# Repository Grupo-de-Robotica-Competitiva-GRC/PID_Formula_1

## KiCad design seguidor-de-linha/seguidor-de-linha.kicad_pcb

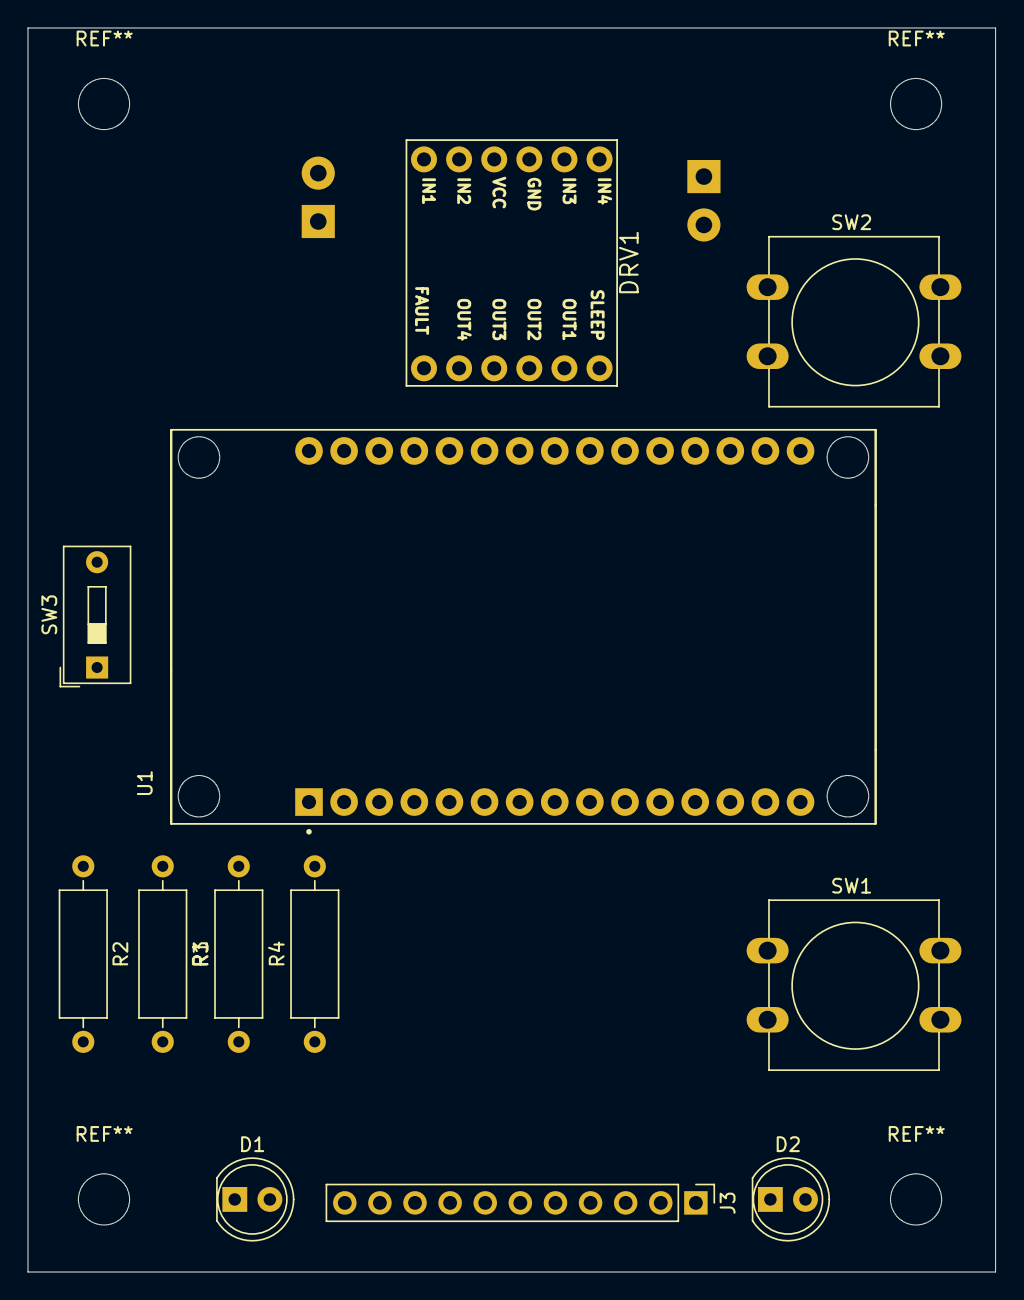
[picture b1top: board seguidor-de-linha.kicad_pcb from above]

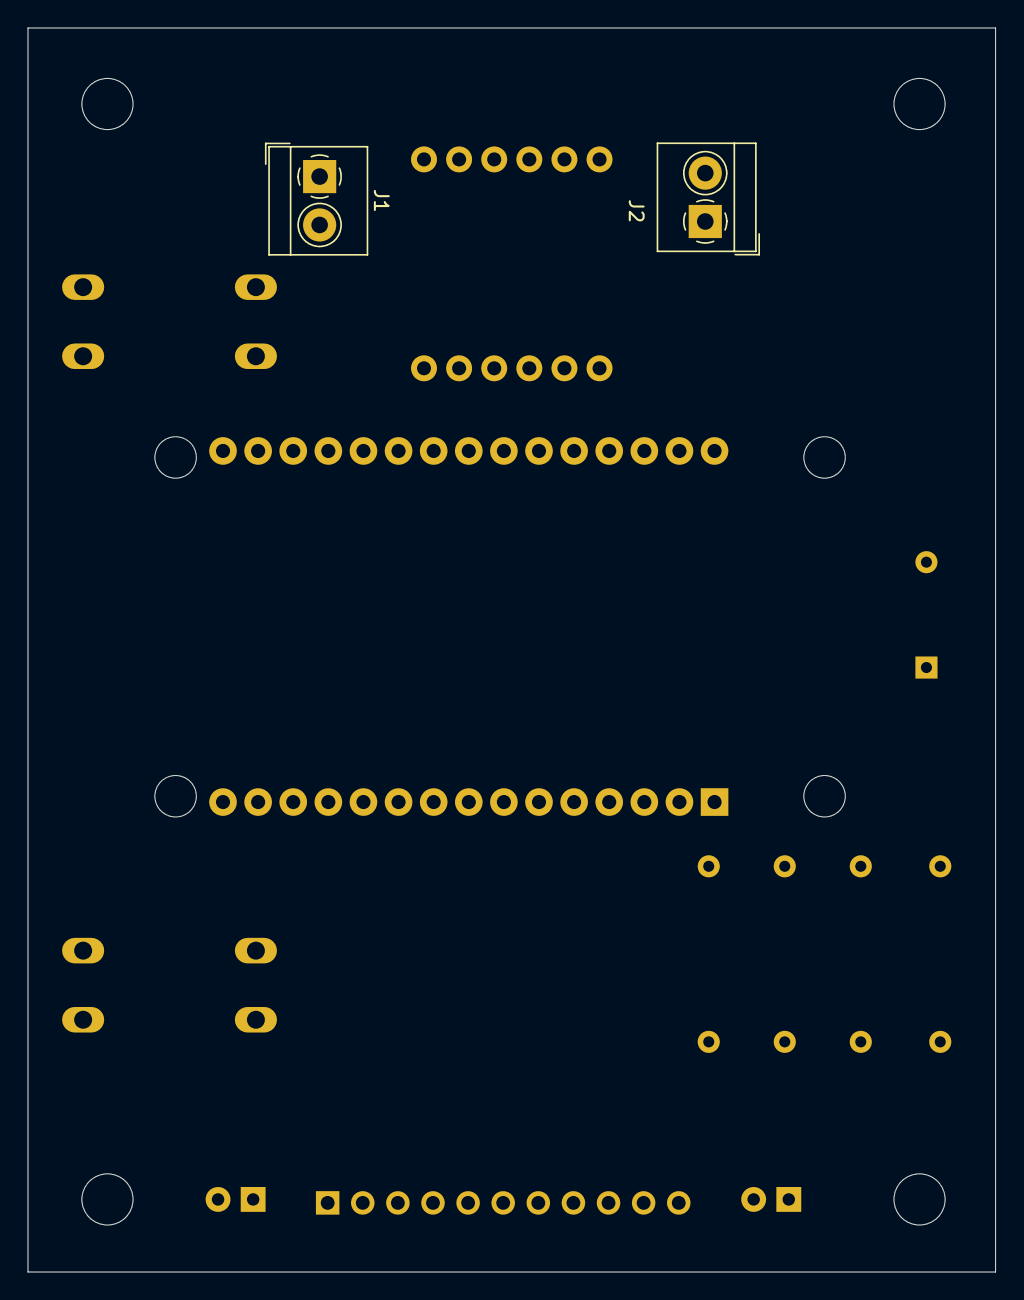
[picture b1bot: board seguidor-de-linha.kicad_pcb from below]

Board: 2 copper layers, 70.0 x 90.0 mm, 14 parts (2 on the bottom side), 26 nets, no tracks yet.

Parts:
D1, D2: LED; LED_D5.0mm
DRV1: drv8833; DRV8833 MOTOR DRIVER
J1, J2: Screw_Terminal_01x02; TerminalBlock_4Ucon_1x02_P3.50mm_Horizontal
J3: Conn_01x11_Female; PinHeader_1x11_P2.54mm_Vertical
R1, R2, R3, R4: R; R_Axial_DIN0309_L9.0mm_D3.2mm_P12.70mm_Horizontal
SW1, SW2: SW_Push; SW_PUSH-12mm
SW3: SW_DPST_x2; SW_DIP_SPSTx01_Slide_9.78x4.72mm_W7.62mm_P2.54mm
U1: ESP32-DEVKIT-V1; MODULE_ESP32_DEVKIT_V1

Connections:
3v3: DRV1.10 (VCC), J3.11, SW1.2, SW2.2, U1.1 (3V3)
7.4V: SW3.2 (B), U1.30 (VIN)
-BATT: DRV1.9 (GND), J3.1, R1.1, R2.1, R3.1, R4.1, U1.2 (GND), U1.29 (GND)
D1: J3.3, U1.4 (D2)
D2: J3.4, U1.5 (D4)
D3: J3.5, U1.8 (D5)
D4: J3.6, U1.9 (D18)
D5: J3.7, U1.10 (D19)
D6: J3.8, U1.6 (RX2)
D7: J3.9, U1.7 (TX2)
D8: J3.10, U1.15 (D23)
IN1: DRV1.12 (IN1), U1.21 (D32)
IN2: DRV1.11 (IN2), U1.22 (D33)
IN3: DRV1.8 (IN3), U1.23 (D25)
IN4: DRV1.7 (IN4), U1.26 (D14)
IR: J3.2, U1.3 (D15)
LED1: D1.2 (A), U1.27 (D12)
LED2: D2.2 (A), U1.28 (D13)
unnamed: D1.1 (K), R1.2
unnamed: D2.1 (K), R2.2
OUT1: DRV1.2 (OUT1), J1.1
OUT2: DRV1.3 (OUT2), J1.2
OUT3: DRV1.4 (OUT3), J2.1
OUT4: DRV1.5 (OUT4), J2.2
PUSH1: R4.2, SW1.1, U1.24 (D26)
PUSH2: R3.2, SW2.1, U1.25 (D27)

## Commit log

2024-03-04 codigo MVP
2024-04-18 modificacoes driver
2024-09-11 Tradução Inicial
2024-10-25 Teste ponte H com pwm e sensores
2024-11-01 expansão dos sensores
2024-11-13 mudança em erro e dutycicle
2024-11-13 removendo ) errados
2024-11-19 codigos em trabalho
    motocontrolavel: if e else, deu bom
    backup_funcionou: Não funcionou nada. Ainda em construção
2024-11-21 PID sem curva de 90º
2024-11-21 Create Sem frescuras ( 4 sensors)
2024-11-21 90º força bruta, inconsistências em curvas
2025-05-23 Create outrotesteComGiroscopio
2025-10-07 Adicionado arquivos de Projeto de esquematico, layout e modelagem 3D
2025-10-07 Adição de esquemático
2025-10-07 Adição de código com 2 rotinas utilizando os 2 cores da ESP-32
2025-10-10 codigo do carrinho pro dtec
2025-10-10 implementando as tesks de calibra e seguir
2025-10-15 ultimaatulizacao do controle PS:ainda nao funfa
2025-10-24 atualizacao -agora ta seguindo a linha
2025-10-28 Bluetooth para atualizar variaveis do PID
2025-10-30 Organização de pastas e decomposicao do codigo em modulos para melhor manutencao ecompreensao
2025-10-30 tirei arquivos desnecessários
2025-10-31 organizando o codigo backup
2025-10-31 Modularização de código principal
2025-10-31 modularização PID
2025-10-31 Modularização completa do firmware (Já pode utilizar)
2025-11-03 Correção do erro da modularização(falta testar)
2025-11-06 nao funfa ainda
2026-04-16 atualizacao para a velocidade atual dos motores
